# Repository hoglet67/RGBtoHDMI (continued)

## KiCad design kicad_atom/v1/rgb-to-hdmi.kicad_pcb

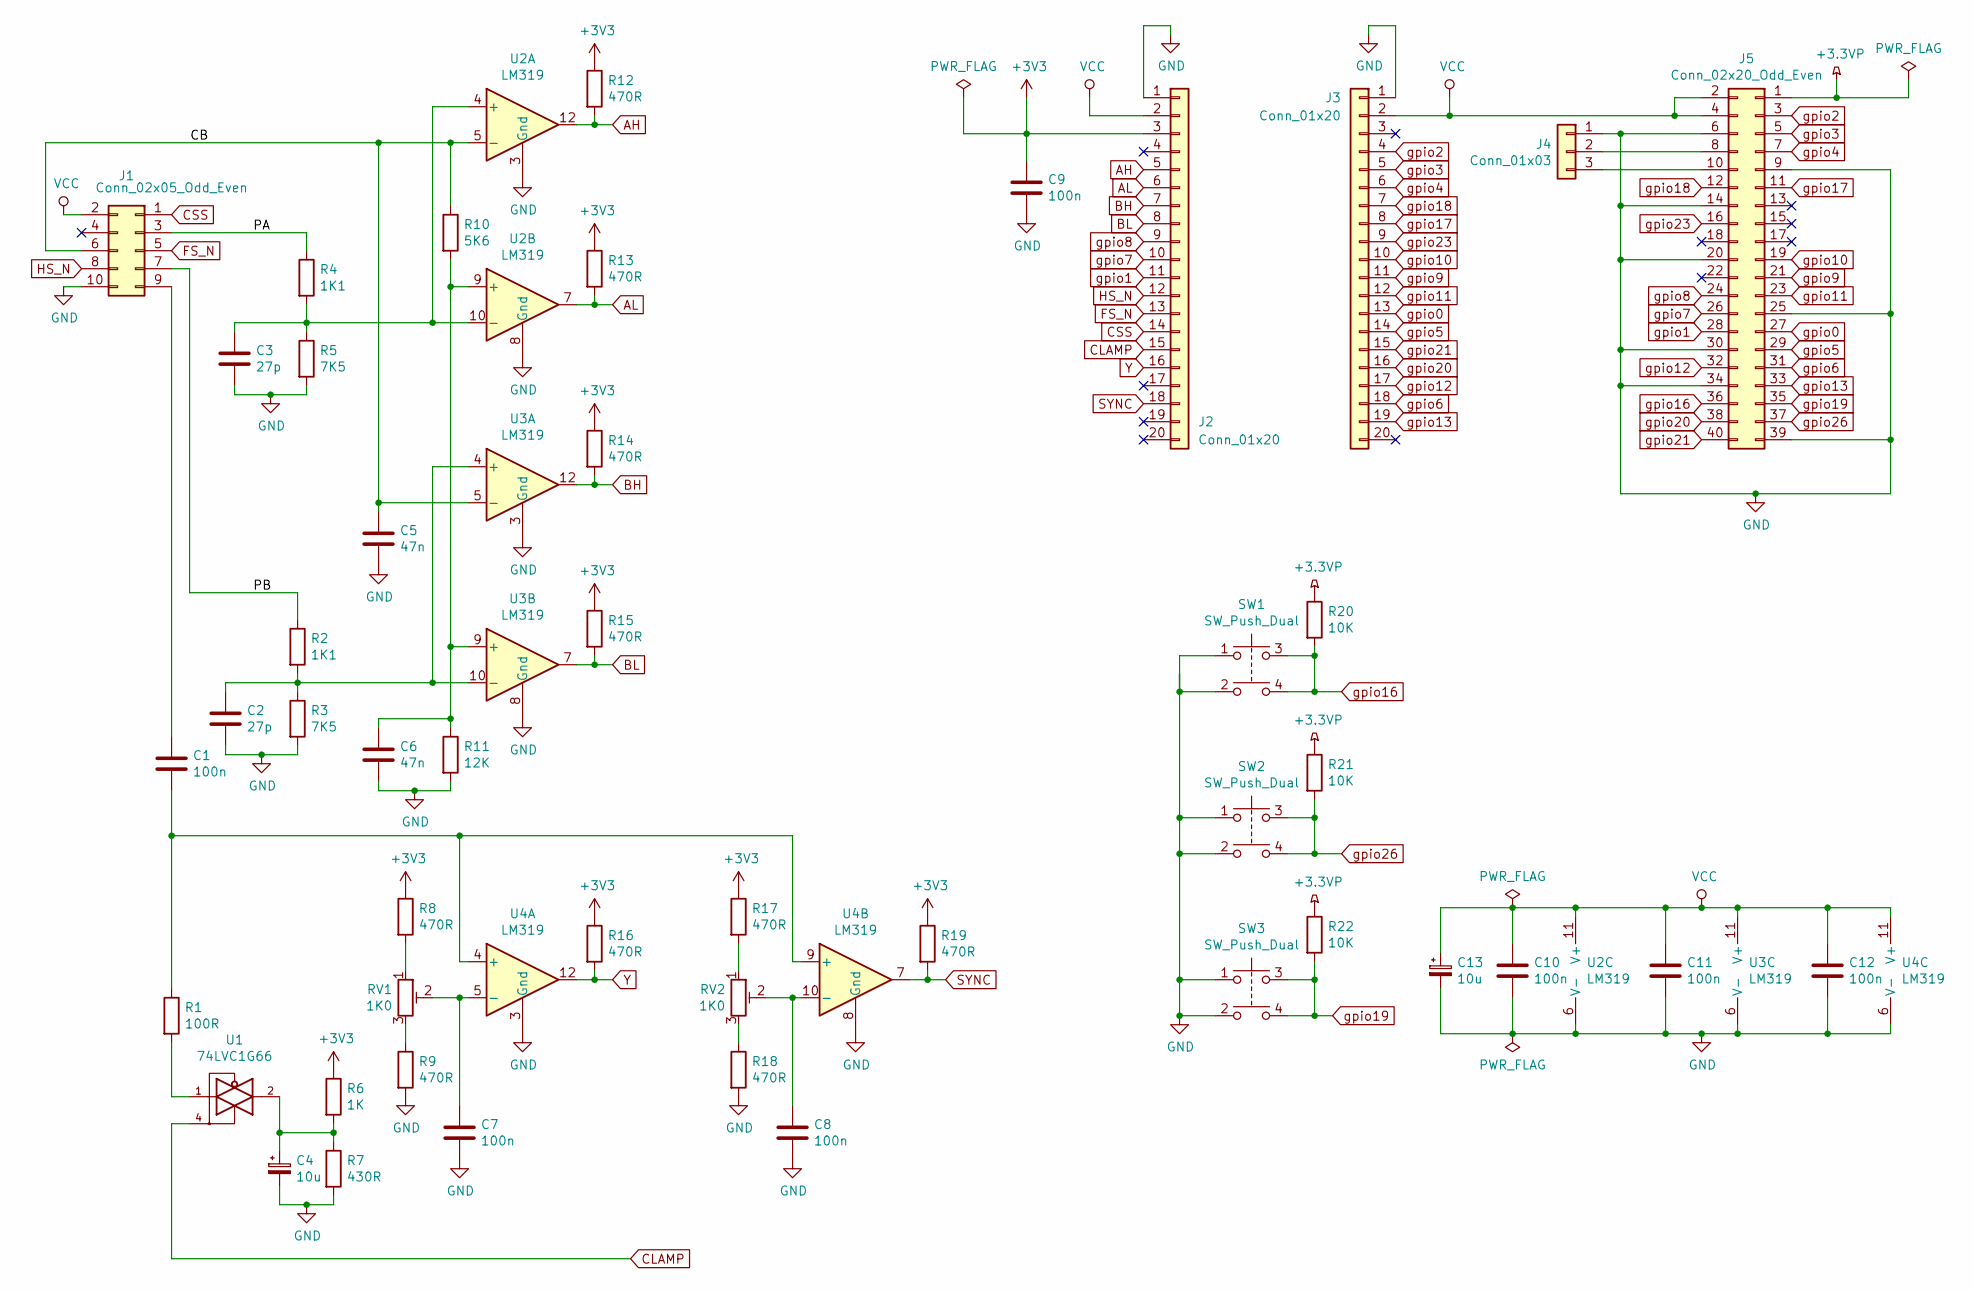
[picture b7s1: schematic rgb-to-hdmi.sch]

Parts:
C1, C7, C8, C9, C10, C11, C12: 100n; C_Rect_L7.0mm_W2.5mm_P5.00mm
C2, C3: 27p; C_Rect_L7.0mm_W2.5mm_P5.00mm
C4, C13: 10u; CP_Radial_D5.0mm_P2.50mm
C5, C6: 47n; C_Rect_L7.0mm_W2.5mm_P5.00mm
J1: Conn_02x05_Odd_Even; PinHeader_2x05_P2.54mm_Vertical
J2, J3: Conn_01x20; PinSocket_1x20_P2.54mm_Vertical
J4: Conn_01x03; PinHeader_1x03_P2.54mm_Vertical
J5: Conn_02x20_Odd_Even; PinSocket_2x20_P2.54mm_Vertical
R1: 100R; R_Axial_DIN0207_L6.3mm_D2.5mm_P10.16mm_Horizontal
R2, R4: 1K1; R_Axial_DIN0207_L6.3mm_D2.5mm_P10.16mm_Horizontal
R3, R5: 7K5; R_Axial_DIN0207_L6.3mm_D2.5mm_P10.16mm_Horizontal
R6: 1K; R_Axial_DIN0207_L6.3mm_D2.5mm_P10.16mm_Horizontal
R7: 430R; R_Axial_DIN0207_L6.3mm_D2.5mm_P10.16mm_Horizontal
R8, R9, R12, R13, R14, R15, R16, R17, R18, R19: 470R; R_Axial_DIN0207_L6.3mm_D2.5mm_P10.16mm_Horizontal
R10: 5K6; R_Axial_DIN0207_L6.3mm_D2.5mm_P10.16mm_Horizontal
R11: 12K; R_Axial_DIN0207_L6.3mm_D2.5mm_P10.16mm_Horizontal
R20, R21, R22: 10K; R_Axial_DIN0207_L6.3mm_D2.5mm_P10.16mm_Horizontal
RV1, RV2: 1K0; Potentiometer_Vishay_T73YP_Vertical
SW1, SW2, SW3: SW_Push_Dual; SW_TH_Tactile_Omron_B3F-10xx
U1: 74LVC1G66; SOT-23-5_HandSoldering
U2, U3, U4: LM319; DIP-14_W7.62mm_Socket_LongPads

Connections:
+3.3VP: J5.1, R20.1, R21.1, R22.1
+3V3: C9.1, J2.3, R6.1, R8.1, R12.1, R13.1, R14.1, R15.1, R16.1, R17.1, R19.1
/CB: C5.1, J1.6, R10.1, U2.5 (-), U3.5 (-)
/PA: J1.3, R4.1
/PB: J1.7, R2.1
AH: J2.5, R12.2, U2.12
AL: J2.6, R13.2, U2.7
BH: J2.7, R14.2, U3.12
BL: J2.8, R15.2, U3.7
CLAMP: J2.15, U1.4
CSS: J1.1, J2.14
FS_N: J1.5, J2.13
GND: C2.2, C3.2, C4.2, C5.2, C6.2, C7.2, C8.2, C9.2, C10.2, C11.2, C12.2, C13.2, J1.10, J2.1, J3.1, J4.1, J5.6, J5.9, J5.14, J5.20, J5.25, J5.30, J5.34, J5.39, R3.2, R5.2, R7.2, R9.2, R11.2, R18.2, SW1.1, SW1.2, SW2.1, SW2.2, SW3.1, SW3.2, U1.3 (GND), U2.3 (Gnd), U2.6 (V-), U2.8 (Gnd), U3.3 (Gnd), U3.6 (V-), U3.8 (Gnd), U4.3 (Gnd), U4.6 (V-), U4.8 (Gnd)
HS_N: J1.8, J2.12
unnamed: C1.1, J1.9
unnamed: C1.2, R1.1, U4.4 (+), U4.9 (+)
unnamed: C2.1, R2.2, R3.1, U3.4 (+), U3.10 (-)
unnamed: C3.1, R4.2, R5.1, U2.4 (+), U2.10 (-)
unnamed: C4.1, R6.2, R7.1, U1.2
unnamed: C6.1, R10.2, R11.1, U2.9 (+), U3.9 (+)
unnamed: C7.1, RV1.2, U4.5 (-)
unnamed: C8.1, RV2.2, U4.10 (-)
unnamed: J4.2, J5.8
unnamed: J4.3, J5.10
unnamed: R1.2, U1.1
unnamed: R8.2, RV1.1
unnamed: R9.1, RV1.3
unnamed: R17.2, RV2.1
unnamed: R18.1, RV2.3
SYNC: J2.18, R19.2, U4.7
VCC: C10.1, C11.1, C12.1, C13.1, J1.2, J2.2, J3.2, J5.2, J5.4, U1.5 (VCC), U2.11 (V+), U3.11 (V+), U4.11 (V+)
Y: J2.16, R16.2, U4.12
gpio0: J3.13, J5.27
gpio1: J2.11, J5.28
gpio2: J3.4, J5.3
gpio3: J3.5, J5.5
gpio4: J3.6, J5.7
gpio5: J3.14, J5.29
gpio6: J3.18, J5.31
gpio7: J2.10, J5.26
gpio8: J2.9, J5.24
gpio9: J3.11, J5.21
gpio10: J3.10, J5.19
gpio11: J3.12, J5.23
gpio12: J3.17, J5.32
gpio13: J3.19, J5.33
gpio16: J5.36, R20.2, SW1.3, SW1.4
gpio17: J3.8, J5.11
gpio18: J3.7, J5.12
gpio19: J5.35, R22.2, SW3.3, SW3.4
gpio20: J3.16, J5.38
gpio21: J3.15, J5.40
gpio23: J3.9, J5.16
gpio26: J5.37, R21.2, SW2.3, SW2.4

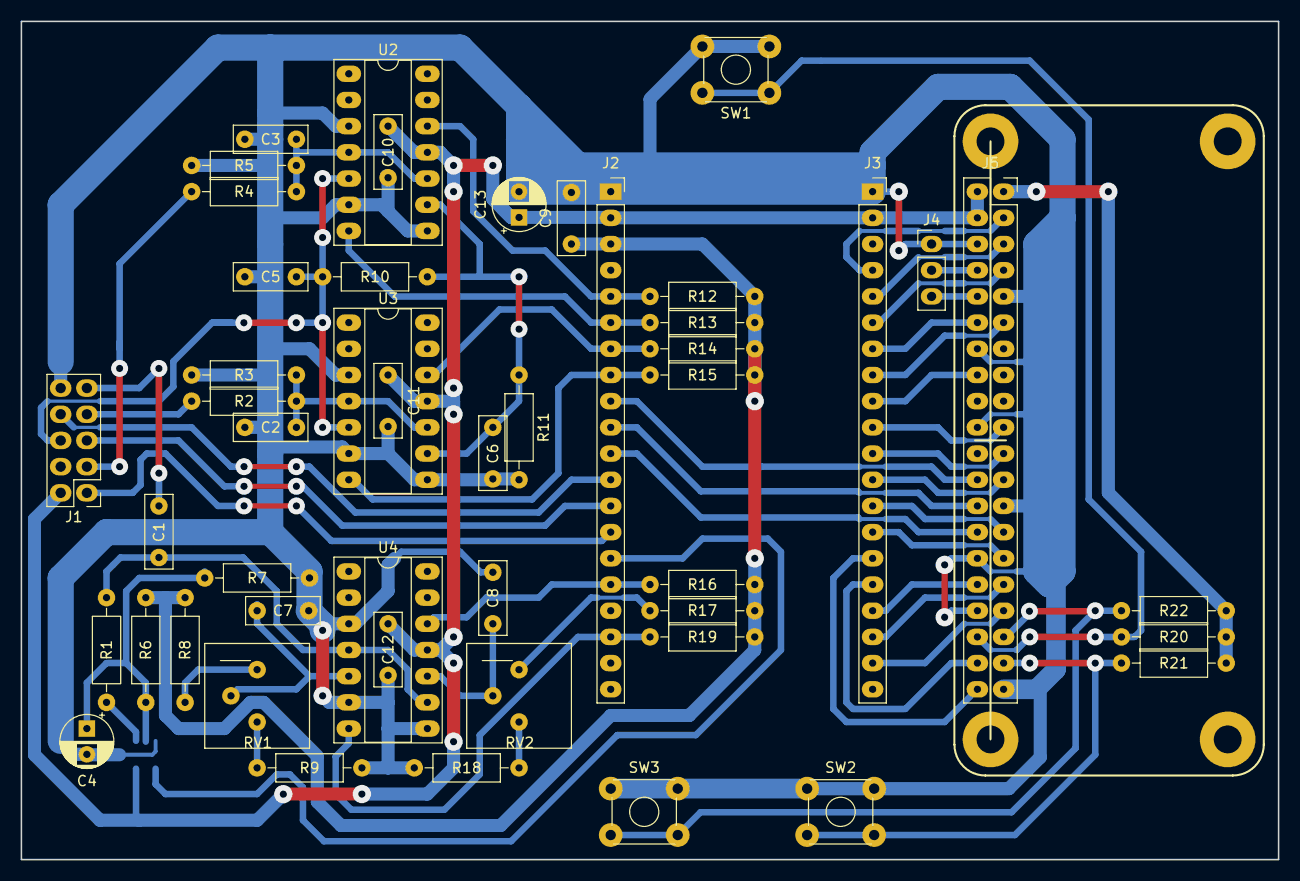
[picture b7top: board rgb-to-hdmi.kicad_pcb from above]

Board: 2 copper layers, 121.9 x 81.3 mm, 49 parts (1 on the bottom side), 54 nets.
